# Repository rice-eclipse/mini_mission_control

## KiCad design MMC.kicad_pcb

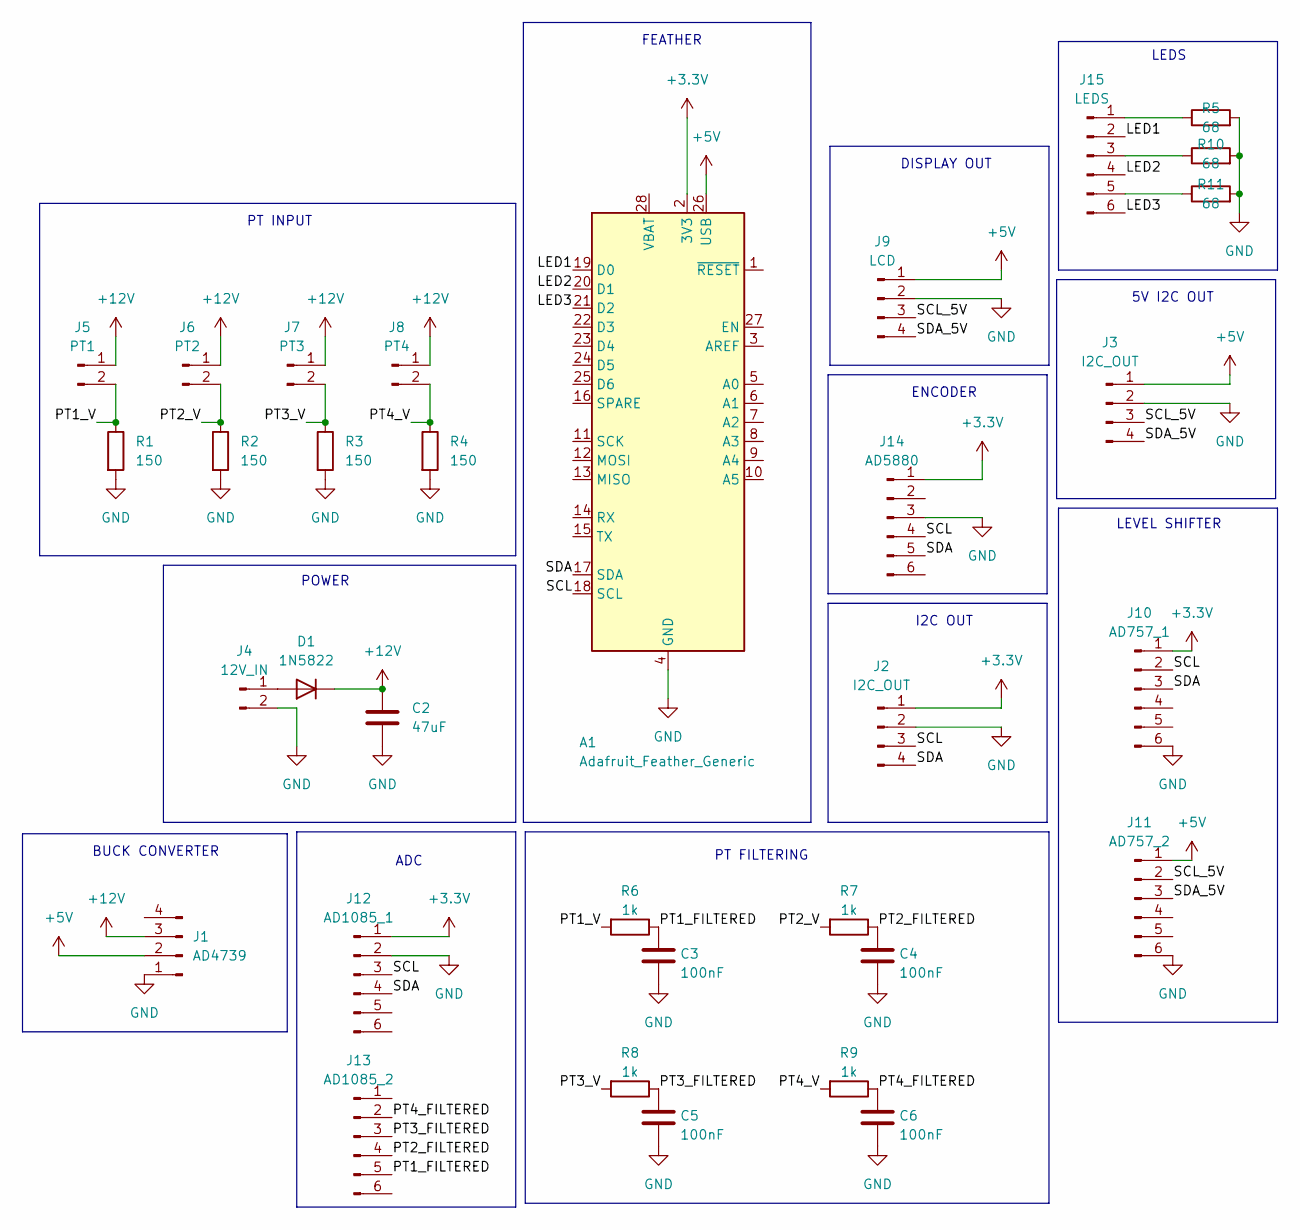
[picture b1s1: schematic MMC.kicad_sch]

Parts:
A1: Adafruit_Feather_Generic; Adafruit_Feather
C2: 47uF; C_1206_3216Metric
C3, C4, C5, C6: 100nF; C_1206_3216Metric
D1: 1N5822; D_5KPW_P12.70mm_Horizontal
J1: AD4739; PinSocket_1x04_P2.54mm_Vertical
J2, J3: I2C_OUT; PinSocket_1x04_P2.54mm_Vertical
J4: 12V_IN; TerminalBlock_4Ucon_1x02_P3.50mm_Horizontal
J5: PT1; TerminalBlock_4Ucon_1x02_P3.50mm_Horizontal
J6: PT2; TerminalBlock_4Ucon_1x02_P3.50mm_Horizontal
J7: PT3; TerminalBlock_4Ucon_1x02_P3.50mm_Horizontal
J8: PT4; TerminalBlock_4Ucon_1x02_P3.50mm_Horizontal
J9: LCD; PinSocket_1x04_P2.54mm_Vertical
J10: AD757_1; PinSocket_1x06_P2.54mm_Vertical
J11: AD757_2; PinSocket_1x06_P2.54mm_Vertical
J12: AD1085_1; PinSocket_1x06_P2.54mm_Vertical
J13: AD1085_2; PinSocket_1x06_P2.54mm_Vertical
J14: AD5880; PinSocket_1x06_P2.54mm_Vertical
J15: LEDS; PinSocket_1x06_P2.54mm_Vertical
R1, R2, R3, R4: 150; R_1206_3216Metric
R5, R10, R11: 68; R_1206_3216Metric
R6, R7, R8, R9: 1k; R_1206_3216Metric

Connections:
+3.3V: A1.2 (3V3), J2.1, J10.1, J12.1, J14.1
+5V: A1.26 (USB), J1.2, J3.1, J9.1, J11.1
+12V: C2.1, D1.1 (K), J1.3, J5.1, J6.1, J7.1, J8.1
/LED1: A1.19 (D0), J15.2
/LED2: A1.20 (D1), J15.4
/LED3: A1.21 (D2), J15.6
/PT1_FILTERED: C3.1, J13.5, R6.1
/PT1_V: J5.2, R1.1, R6.2
/PT2_FILTERED: C4.1, J13.4, R7.1
/PT2_V: J6.2, R2.1, R7.2
/PT3_FILTERED: C5.1, J13.3, R8.1
/PT3_V: J7.2, R3.1, R8.2
/PT4_FILTERED: C6.1, J13.2, R9.1
/PT4_V: J8.2, R4.1, R9.2
/SCL: A1.18 (SCL), J2.3, J10.2, J12.3, J14.4
/SCL_5V: J3.3, J9.3, J11.2
/SDA: A1.17 (SDA), J2.4, J10.3, J12.4, J14.5
/SDA_5V: J3.4, J9.4, J11.3
GND: A1.4 (GND), C2.2, C3.2, C4.2, C5.2, C6.2, J1.1, J2.2, J3.2, J4.2, J9.2, J10.6, J11.6, J12.2, J14.3, R1.2, R2.2, R3.2, R4.2, R5.2, R10.2, R11.2
unnamed: D1.2 (A), J4.1
unnamed: J15.1, R5.1
unnamed: J15.3, R10.1
unnamed: J15.5, R11.1

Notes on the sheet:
5V I2C OUT
POWER
DISPLAY OUT
PT INPUT
BUCK CONVERTER
ENCODER
I2C OUT
PT FILTERING
LEVEL SHIFTER
FEATHER
ADC
LEDS

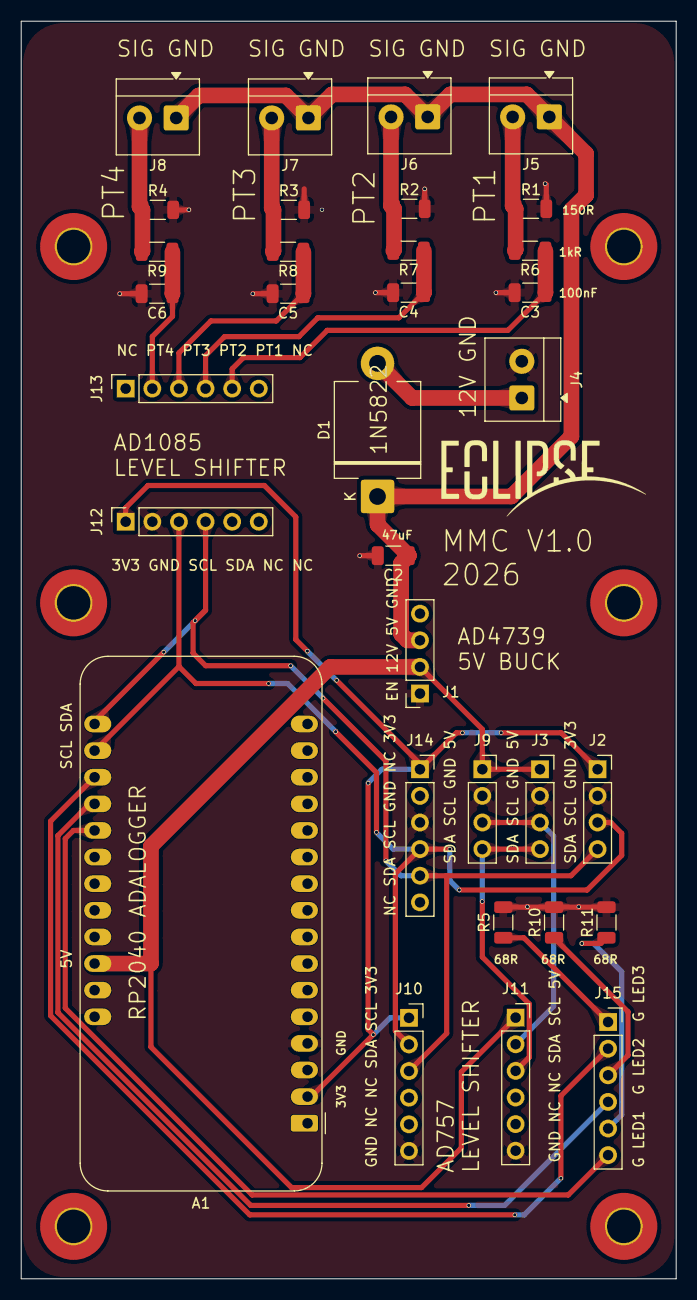
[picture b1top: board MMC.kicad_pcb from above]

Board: 2 copper layers, 62.5 x 120.0 mm, 33 parts (0 on the bottom side), 23 nets.
